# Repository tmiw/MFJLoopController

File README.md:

# MFJLoopController
A ESP8266-based remote controller for MFJ magnetic loops.

## Prerequisites

* WEMOS D1 mini Lite development board (or clone). [Example](https://www.amazon.com/gp/product/B081PX9YFV/ref=ppx_yo_dt_b_asin_title_o03_s00?ie=UTF8&psc=1)
* [Adafruit ADS1115 ADC](https://www.adafruit.com/product/1085)
* Arduino IDE with ESP boards and [LittleFS data uploader tool](https://arduino-esp8266.readthedocs.io/en/latest/filesystem.html#uploading-files-to-file-system) installed
* [MFJ Bias Tee](https://mfjenterprises.com/products/mfj-4116)
* [H bridge circuit](http://www.modularcircuits.com/blog/articles/h-bridge-secrets/h-bridges-the-basics/) to produce +/- 12V. Initial tests done with [LED based solid state relays](https://www.mouser.com/ProductDetail/IXYS-Integrated-Circuits/LCC120?qs=TzJIIqIe2vmIthf%252BEZpoaA%3D%3D) linked together in series to reduce required pin count to 2 (one for each direction).
* Isolated power supply (e.g. **NOT** connected to radio's ground). [This Mouser project](https://www.mouser.com/ProjectManager/ProjectDetail.aspx?AccessID=d2ae561f5a) seems to work reasonably well in initial testing to permit sharing 12V power supply with rest of shack (see datasheets for the TMR 9-1212 for required support circuitry to reduce possible RFI).
* Soon: SWR bridge capable of reading 100W and providing 3.3V max analog signals to the ADS1115 ([possible option](https://en.golb.be/automatic-magnetic-loop-tuner-swr-bridge/))

## Setup

1. Set configuration options (pins, Wi-Fi info, etc.) in config.h.
2. Build and upload software using Arduino IDE to device. *Note: the initial upload must be done using USB or UART; subsequent uploads can be done OTA.*
3. Upload filesystem using Tools > ESP8266 LittleFS Data Upload in the Arduino IDE.

## Usage

By default, the software uses DHCP to get an IP address. Simply go to its assigned IP address on port 80 in a Web browser and click on the desired tuning direction buttons; releasing the associated button results in tuning stop. Note that you're looking for maximum signal/noise for the initial pass at tuning; the eventual auto-tune feature will perform fine tuning for minimal SWR.

## To Do

* Auto-tuning
* SSL support?
* PCB combining all hardware and eliminating loose wires

## License

BSD 3-clause (TBD)

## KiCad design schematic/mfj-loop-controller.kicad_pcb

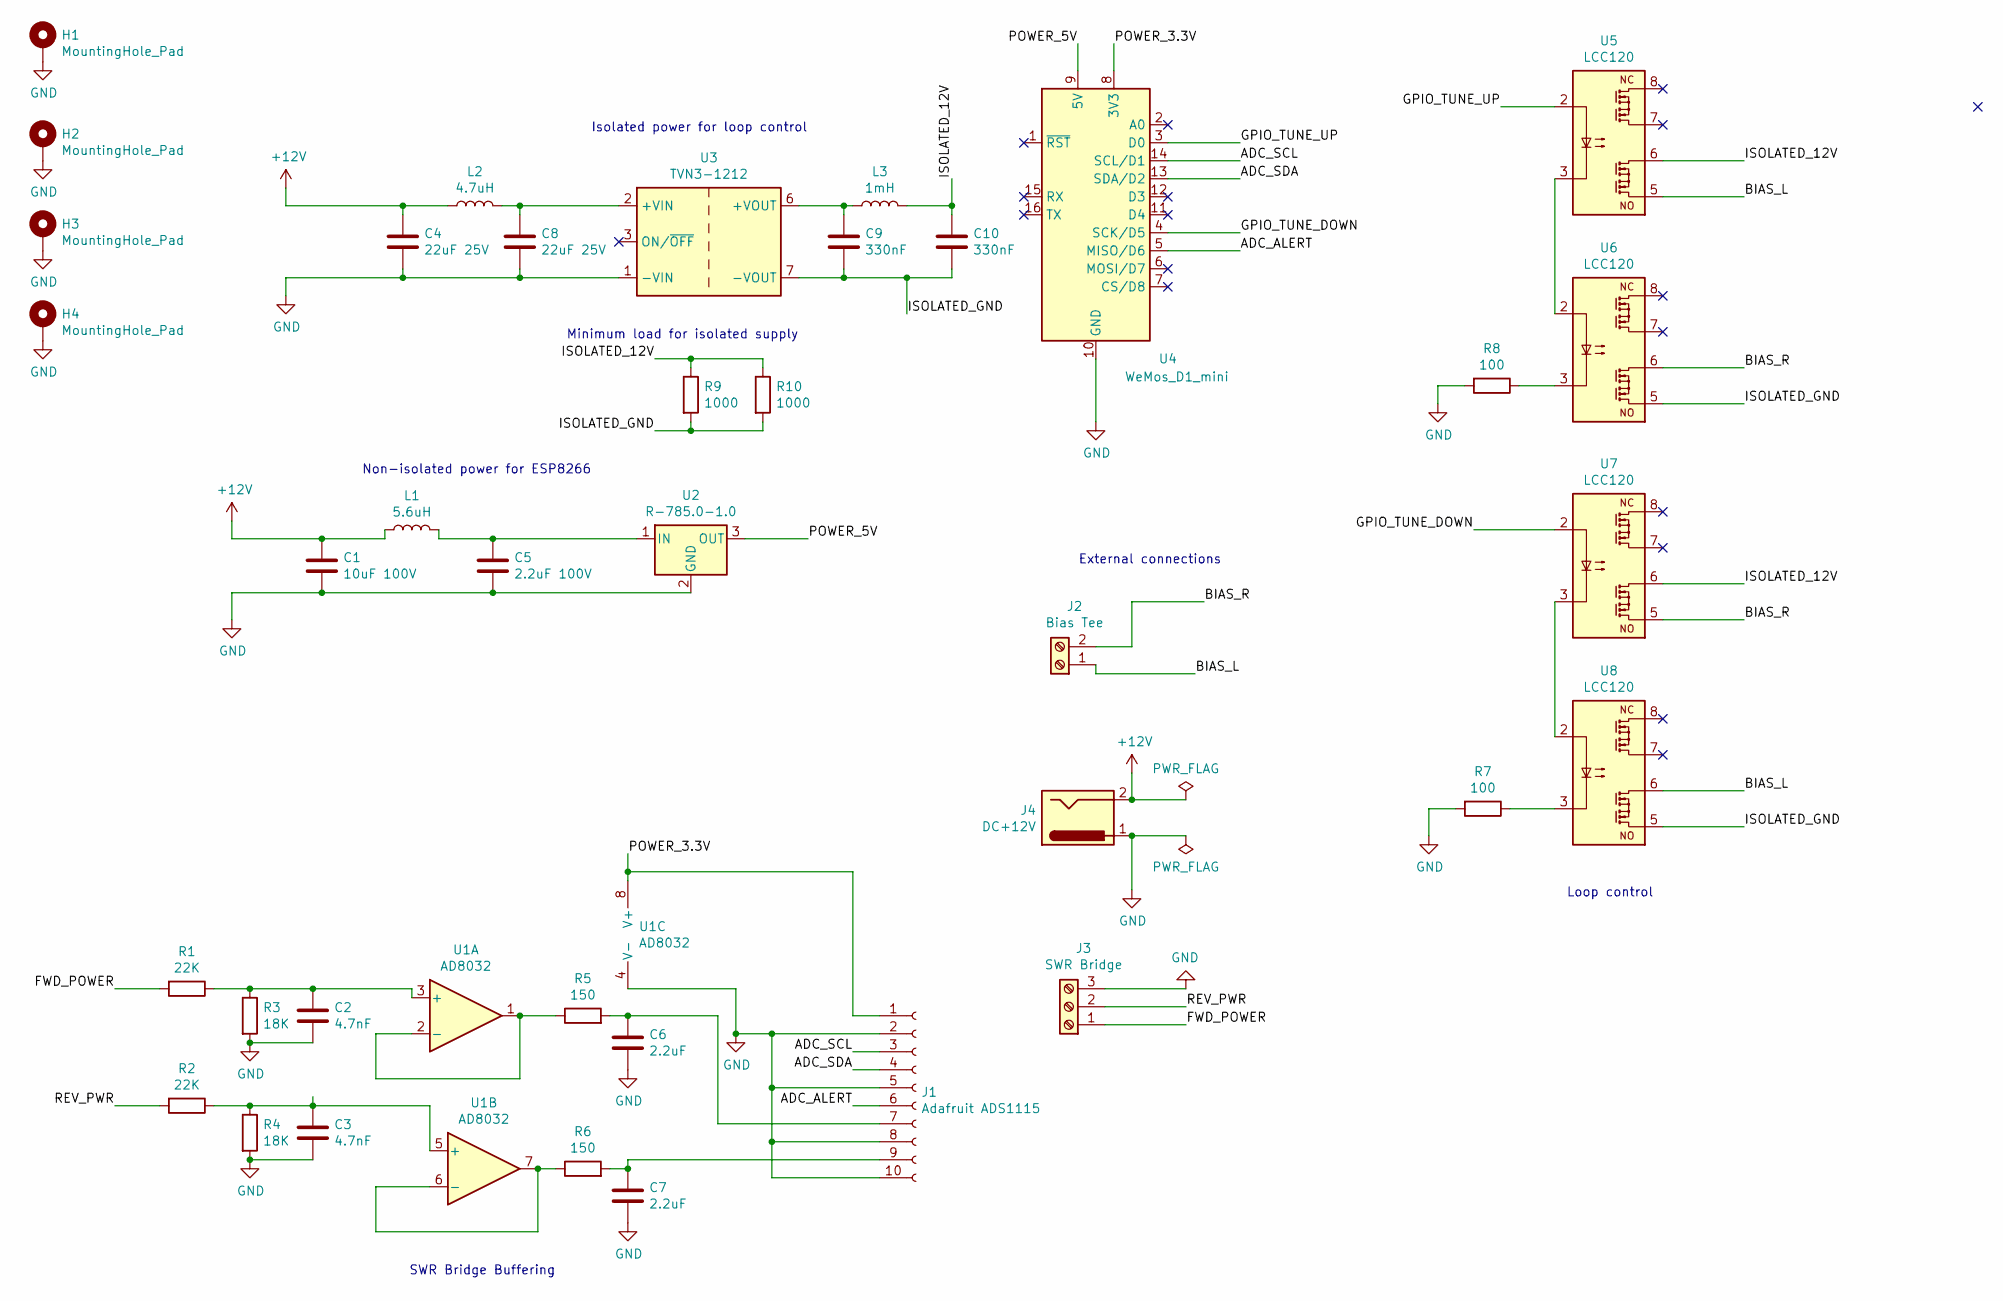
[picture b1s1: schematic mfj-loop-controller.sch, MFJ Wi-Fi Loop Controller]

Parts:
C1: 10uF 100V; C_Axial_L5.1mm_D3.1mm_P7.50mm_Horizontal
C2, C3: 4.7nF; C_Axial_L5.1mm_D3.1mm_P7.50mm_Horizontal
C4, C8: 22uF 25V; C_Axial_L5.1mm_D3.1mm_P7.50mm_Horizontal
C5: 2.2uF 100V; C_Axial_L5.1mm_D3.1mm_P7.50mm_Horizontal
C6, C7: 2.2uF; C_Axial_L5.1mm_D3.1mm_P7.50mm_Horizontal
C9, C10: 330nF; C_Axial_L5.1mm_D3.1mm_P7.50mm_Horizontal
H1, H2, H3, H4: MountingHole_Pad; MountingHole_3.2mm_M3_DIN965_Pad_TopBottom
J1: Adafruit ADS1115; PinHeader_1x10_P2.54mm_Vertical
J2: Bias Tee; TerminalBlock_bornier-2_P5.08mm
J3: SWR Bridge; TerminalBlock_bornier-3_P5.08mm
J4: DC+12V; BarrelJack_CUI_PJ-063AH_Horizontal_CircularHoles
L1: 5.6uH; L_Axial_L5.3mm_D2.2mm_P10.16mm_Horizontal_Vishay_IM-1
L2: 4.7uH; L_Axial_L5.3mm_D2.2mm_P10.16mm_Horizontal_Vishay_IM-1
L3: 1mH; L_Axial_L5.3mm_D2.2mm_P10.16mm_Horizontal_Vishay_IM-1
R1, R2: 22K; R_Axial_DIN0207_L6.3mm_D2.5mm_P10.16mm_Horizontal
R3, R4: 18K; R_Axial_DIN0207_L6.3mm_D2.5mm_P10.16mm_Horizontal
R5, R6: 150; R_Axial_DIN0207_L6.3mm_D2.5mm_P10.16mm_Horizontal
R7, R8: 100; R_Axial_DIN0207_L6.3mm_D2.5mm_P10.16mm_Horizontal
R9, R10: 1000; R_Axial_DIN0207_L6.3mm_D2.5mm_P10.16mm_Horizontal
U1: AD8032; DIP-8_W7.62mm_Socket
U2: R-785.0-1.0; Converter_DCDC_RECOM_R-78E-0.5_THT
U3: TVN3-1212; Converter_DCDC_TRACO_TMR-xxxx_THT
U4: WeMos_D1_mini; WEMOS_D1_mini_light
U5, U6, U7, U8: LCC120; DIP-8_W7.62mm_Socket

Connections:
+12V: C1.1, C4.1, J4.2, L1.1, L2.1
/ADC_ALERT: J1.6, U4.5 (MISO/D6)
/ADC_SCL: J1.3, U4.14 (SCL/D1)
/ADC_SDA: J1.4, U4.13 (SDA/D2)
/BIAS_L: J2.1, U5.5, U8.6
/BIAS_R: J2.2, U6.6, U7.5
/FWD_POWER: J3.1, R1.2
/GPIO_TUNE_DOWN: U4.4 (SCK/D5), U7.2
/GPIO_TUNE_UP: U4.3 (D0), U5.2
/ISOLATED_12V: C10.1, L3.2, R9.1, R10.1, U5.6, U7.6
/ISOLATED_GND: C9.2, C10.2, R9.2, R10.2, U3.7 (-VOUT), U6.5, U8.5
/POWER_3.3V: J1.1, U1.8 (V+), U4.8 (3V3)
/POWER_5V: U2.3 (OUT), U4.9 (5V)
/REV_PWR: J3.2, R2.2
GND: C1.2, C2.2, C3.2, C4.2, C5.2, C6.2, C7.2, C8.2, H1.1, H2.1, H3.1, H4.1, J1.2, J1.5, J1.8, J1.10, J3.3, J4.1, R3.2, R4.2, R7.2, R8.2, U1.4 (V-), U2.2 (GND), U3.1 (-VIN), U4.10 (GND)
unnamed: C2.1, R1.1, R3.1, U1.3 (+)
unnamed: C3.1, R2.1, R4.1, U1.5 (+)
unnamed: C5.1, L1.2, U2.1 (IN)
unnamed: C6.1, J1.7, R5.2
unnamed: C7.1, J1.9, R6.2
unnamed: C8.1, L2.2, U3.2 (+VIN)
unnamed: C9.1, L3.1, U3.6 (+VOUT)
unnamed: R5.1, U1.1, U1.2 (-)
unnamed: R6.1, U1.6 (-), U1.7
unnamed: R7.1, U8.3
unnamed: R8.1, U6.3
unnamed: U5.3, U6.2
unnamed: U7.3, U8.2

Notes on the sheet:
Minimum load for isolated supply
Isolated power for loop control
Non-isolated power for ESP8266
SWR Bridge Buffering
Loop control
External connections

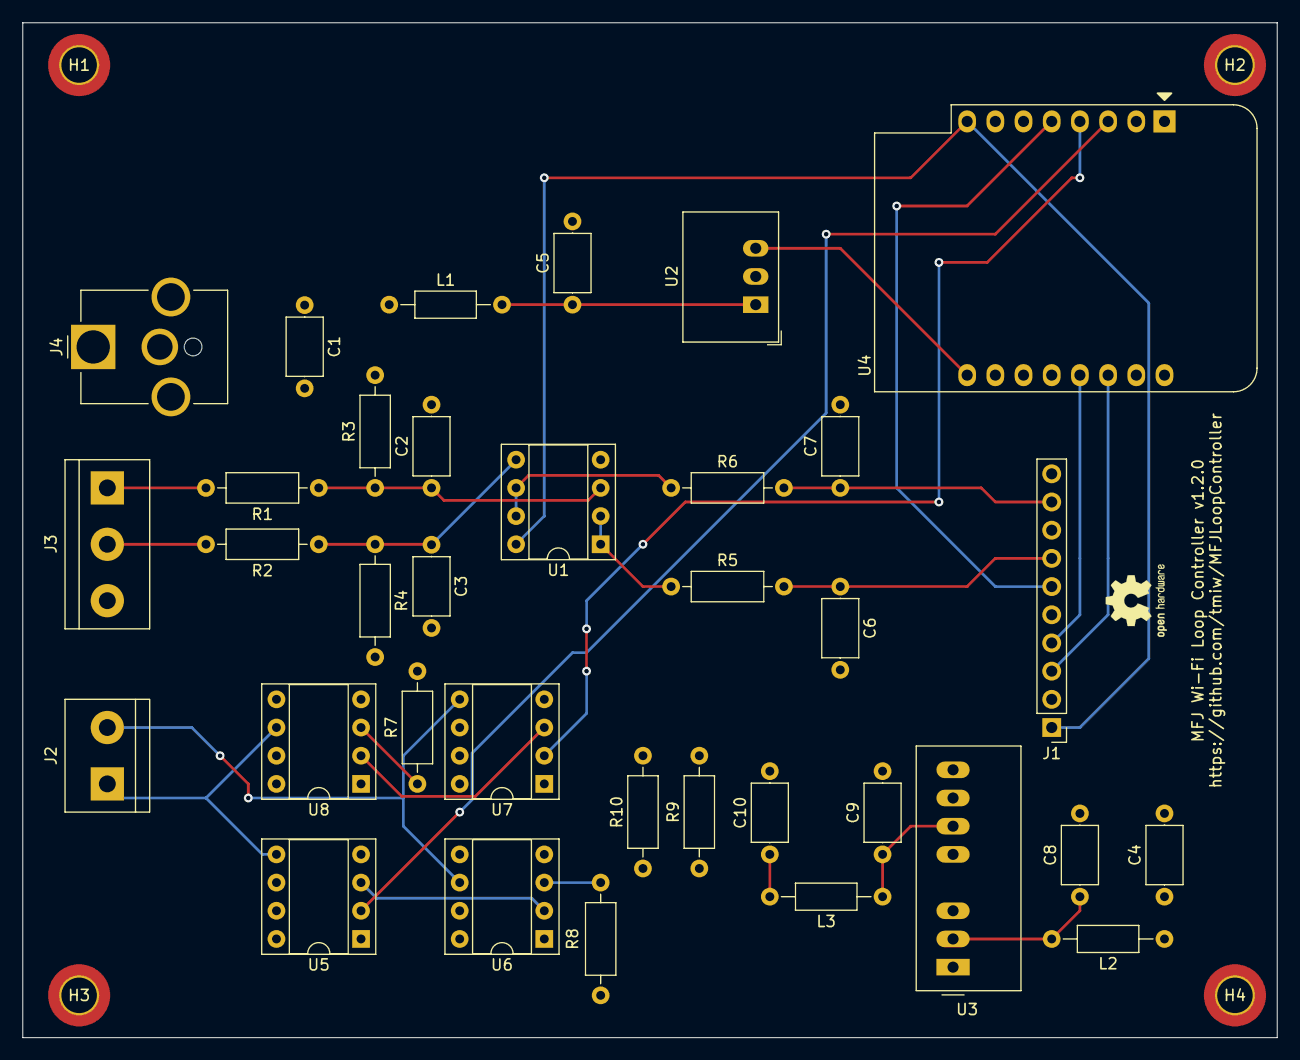
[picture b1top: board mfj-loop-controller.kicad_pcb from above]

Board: 4 copper layers, 113.0 x 91.4 mm, 39 parts (0 on the bottom side), 28 nets.

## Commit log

2020-10-12 Add setup and prerequisites
2020-10-12 Add files from initial prototype.
2020-10-12 Rename ino file to match folder naming.
2020-10-12 Add 50ms pause for pulse after disabling pins.
2020-10-12 Fix typo in README.
2020-10-12 Ignore .DS_Ignore and remove existing files.
2020-10-14 Use preliminary equations for forward/reverse power.
2020-10-14 Cleanup unneeded configuration options.
2020-10-16 Initial pass at non-IRQ based autotune algorithm.
2020-10-18 Initial schematic and PCB for tuner board.
2020-10-18 Initial auto-tune implementation.
2020-10-18 Update PCB markings and version info.
2020-10-24 Adjust equation for FW power based on new numbers from PCB.
2020-10-24 Slow tune timing updates + formatting tweakings.
2020-10-24 Have browser control slow tune and not device to enable easier control.
2020-10-25 Blink ESP board LED during tuning for debugging.
2020-10-25 Use same ADC->watts equation for both fwd/rev power.
2020-10-25 More manual tuning speed tweaks.
2020-10-27 Send large pulse on changing directions to overcome capacitor inertia.
2020-10-27 Autotune/ADC experiments.
2020-10-27 Cleanup.
2020-10-27 Move Wi-Fi config to separate include file.
2020-10-27 Use actual working IIR filter and update SWR calculation.
2020-10-28 Semi-working autotune algorithm (only in slow mode).
2020-10-31 Update schematic and PCB to v1.1.0:
    1. Shrink board footprint to ~4x3" for ease of mounting/EMI compliance.
    2. Add mounting holes to corners.
    3. Add GND/+12V flood fill layers for EMI compliance/routing.
    4. Increase size of R/C/L component footprints for ease of assembly.
    5. Add route for ADC alert pin to ESP82xx board.
    6. Add routes for ADC analog negative pins to ground.
2020-10-31 Update design rules.
2020-11-01 Minor tweaks to PCB.
2020-11-04 Use interrupts to read current ADC values more quickly.
2020-11-05 Don't block system while emitting tuning pulses.
2020-11-06 Reliable loop auto-tuning in slow mode + re-calibration of power meter
2020-11-06 Code cleanup.
2020-11-06 Timing fine tuning
2020-11-12 Major changes to firmware:
    1. Use WebSockets for commands and status updates (to allow for smoother UI).
    2. Use timings corresponding to original MFJ loop tuner control box.
    3. Reenable fast tuning step for autotuning (in progress).
    4. Add delay states between auto-tuning steps to allow for SWR to stabilize.
2020-11-14 Check in in-progress work.
2020-11-17 Rotate power jack 180 degrees on PCB.
2020-11-17 Use fabs in order to fix bugs with SWR reporting.
2020-11-18 Add minimum load to 12V isolated supply to reduce tuning noise.
2020-11-19 Fix WebSocket cleanup to improve reliability.
2020-11-19 Auto-reopen WebSocket on disconnect.
2020-11-19 Switch JSON status output to using Arduino JSON library.
2020-11-19 Request initial status from the board when connecting the WEbSocket.
2020-11-19 Fine tune timing adjustments + formatting tweaks
2020-11-20 Fixed bugs in autotuning.
2020-11-22 Hardware version 1.2.0:
    1. Change 12V isolated supply to "low ripple/noise" version (TVN 3-1212).
    2. Add/update required filtering to reflect TVN 3-1212 and to further reduce ripple.
    3. Reroute isolated section to shorten traces and to use isolated power/ground planes (EMI reduction).
    4. Add optional (?) "minimum load" resistors for use if TVN 3-1212 requires them for proper operation while idle/slow tuning.
2020-11-24 Increase Wi-Fi reliability.
2020-11-24 Continued reliability improvements.
2020-11-25 Fix iterator issue causing software exception to be thrown.
2020-11-25 Revert back to streamFile() implementation of static file serving.
2020-11-25 Tweaks to make the SWR calculation more stable with SDRs.
2021-01-11 Send websocket pings after 30 seconds of inactivity.
2021-01-11 Clean up existing connections if we disconnect from the network.
2021-04-17 Fix issue with HTML causing Chrome/device to eventually lock up.
2021-05-29 Add one shot mode to make the web based controls less touchy on higher bands.
